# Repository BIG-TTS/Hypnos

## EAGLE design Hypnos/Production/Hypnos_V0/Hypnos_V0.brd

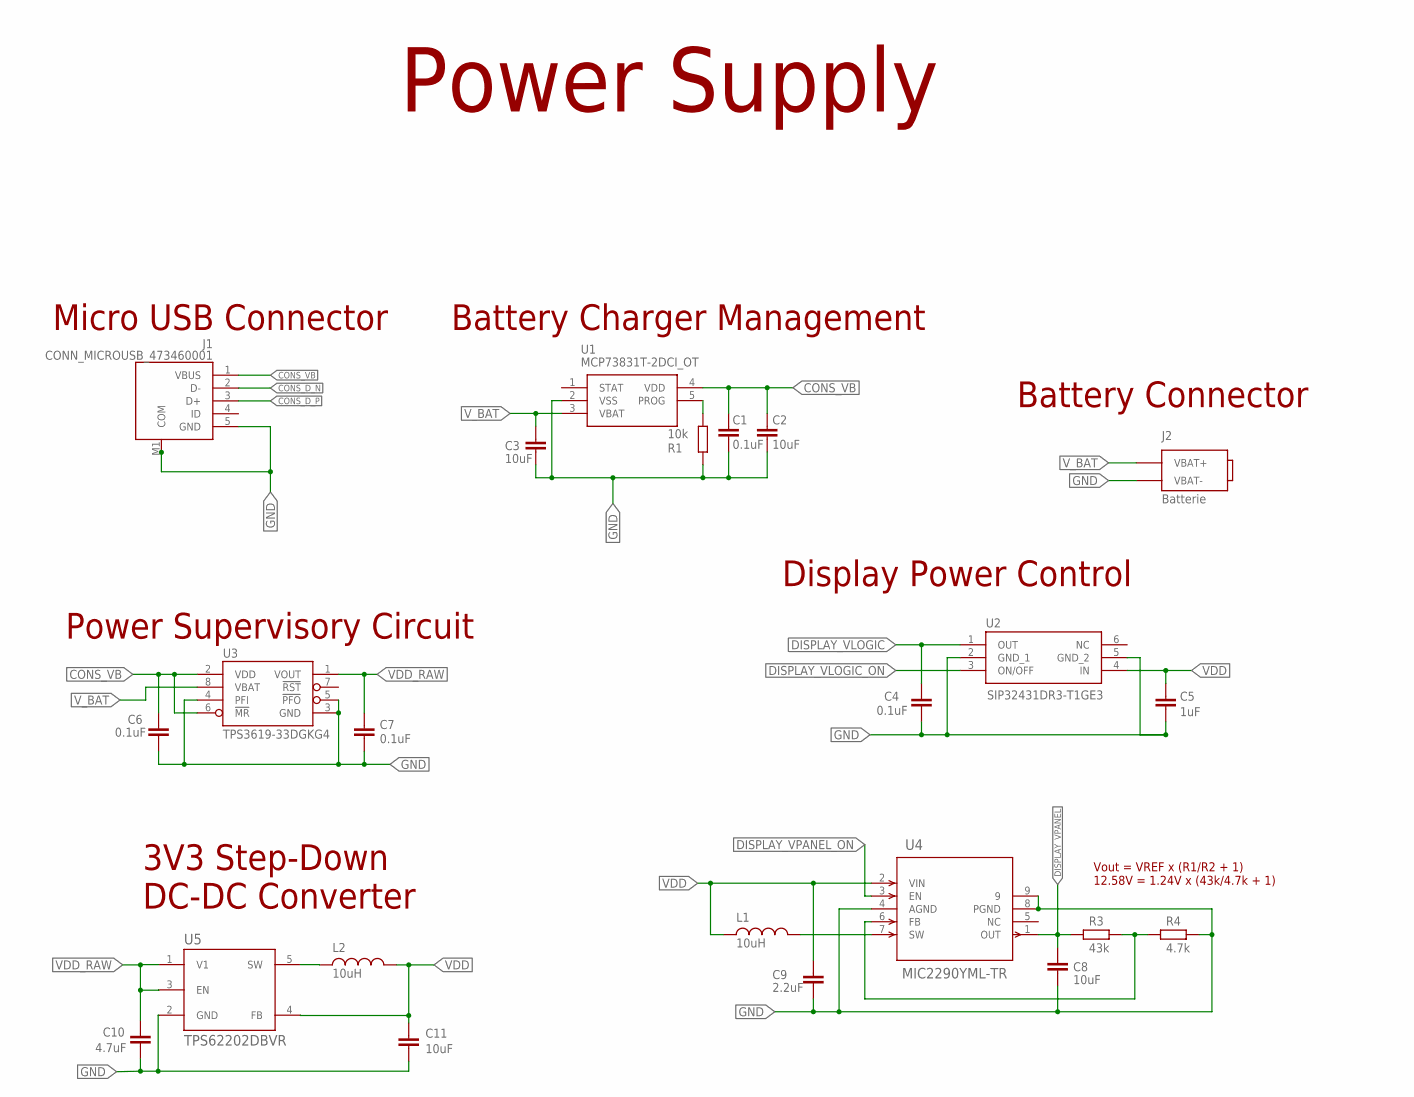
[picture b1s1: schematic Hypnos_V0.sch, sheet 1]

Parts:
C1, C4, C6, C7: 0.1uF; C0603K
C2, C3, C8, C11: 10uF; C0603K
C5: 1uF; C0603K
C9: 2.2uF; C0603K
C10: 4.7uF; C0603K
J1: CONN_MICROUSB_473460001; CONN_MOLEX_473460001
J2: Batterie; BATTERIE
L1, L2: 10uH; L1210
R1: 10k; R0603
R3: 43k; R0603
R4: 4.7k; R0603
U1: MCP73831T-2DCI_OT; SOT95P270X145-5N
U2: SIP32431DR3-T1GE3; SOT65P210X110-6N
U3: TPS3619-33DGKG4; MSOP8
U4: MIC2290YML-TR; MLF-8_ML_MCH
U5: TPS62202DBVR; SOT95P280X145-5N

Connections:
CONS_D_N: J1.2 (D-); also elsewhere on the board
CONS_D_P: J1.3 (D+); also elsewhere on the board
CONS_VB: C1.1, C2.1, C6.1, J1.1 (VBUS), U1.4 (VDD), U3.2 (VDD), U3.6 (!MR); also elsewhere on the board
DISPLAY_VLOGIC: C4.1, U2.1 (OUT); also elsewhere on the board
DISPLAY_VLOGIC_ON: U2.3 (ON/OFF); also elsewhere on the board
DISPLAY_VPANEL: C8.1, R3.2, U4.1 (OUT); also elsewhere on the board
DISPLAY_VPANEL_ON: U4.3 (EN); also elsewhere on the board
FB: R3.1, R4.2, U4.6 (FB)
GND: C1.2, C2.2, C3.2, C4.2, C5.2, C6.2, C7.2, C8.2, C9.2, C10.2, C11.2, J1.5 (GND), J1.M1 (COM), J1.M2 (COM), J1.M3 (COM), J1.M4 (COM), J1.M5 (COM), J1.M6 (COM), J2.2 (VBAT-), R1.2, R4.1, U1.2 (VSS), U2.2 (GND_1), U2.5 (GND_2), U3.3 (GND), U3.4 (PFI), U3.5 (!PFO), U4.4 (AGND), U4.8 (PGND), U4.9, U5.2 (GND); also elsewhere on the board
unnamed: L2.1, U5.5 (SW)
PROG: R1.1, U1.5 (PROG)
SW: L1.2, U4.7 (SW)
VDD: C5.1, C9.1, C11.1, L1.1, L2.2, U2.4 (IN), U4.2 (VIN), U5.4 (FB); also elsewhere on the board
VDD_RAW: C7.1, C10.1, U3.1 (VOUT), U5.1 (V1), U5.3 (EN)
V_BAT: C3.1, J2.1 (VBAT+), U1.3 (VBAT), U3.8 (VBAT)

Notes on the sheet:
Micro USB Connector
Battery Charger Management
Power Supervisory Circuit
Power Supply
3V3 Step-Down DC-DC Converter
Battery Connector
Display Power Control
Vout = VREF x (R1/R2 + 1) 12.58V = 1.24V x (43k/4.7k + 1)

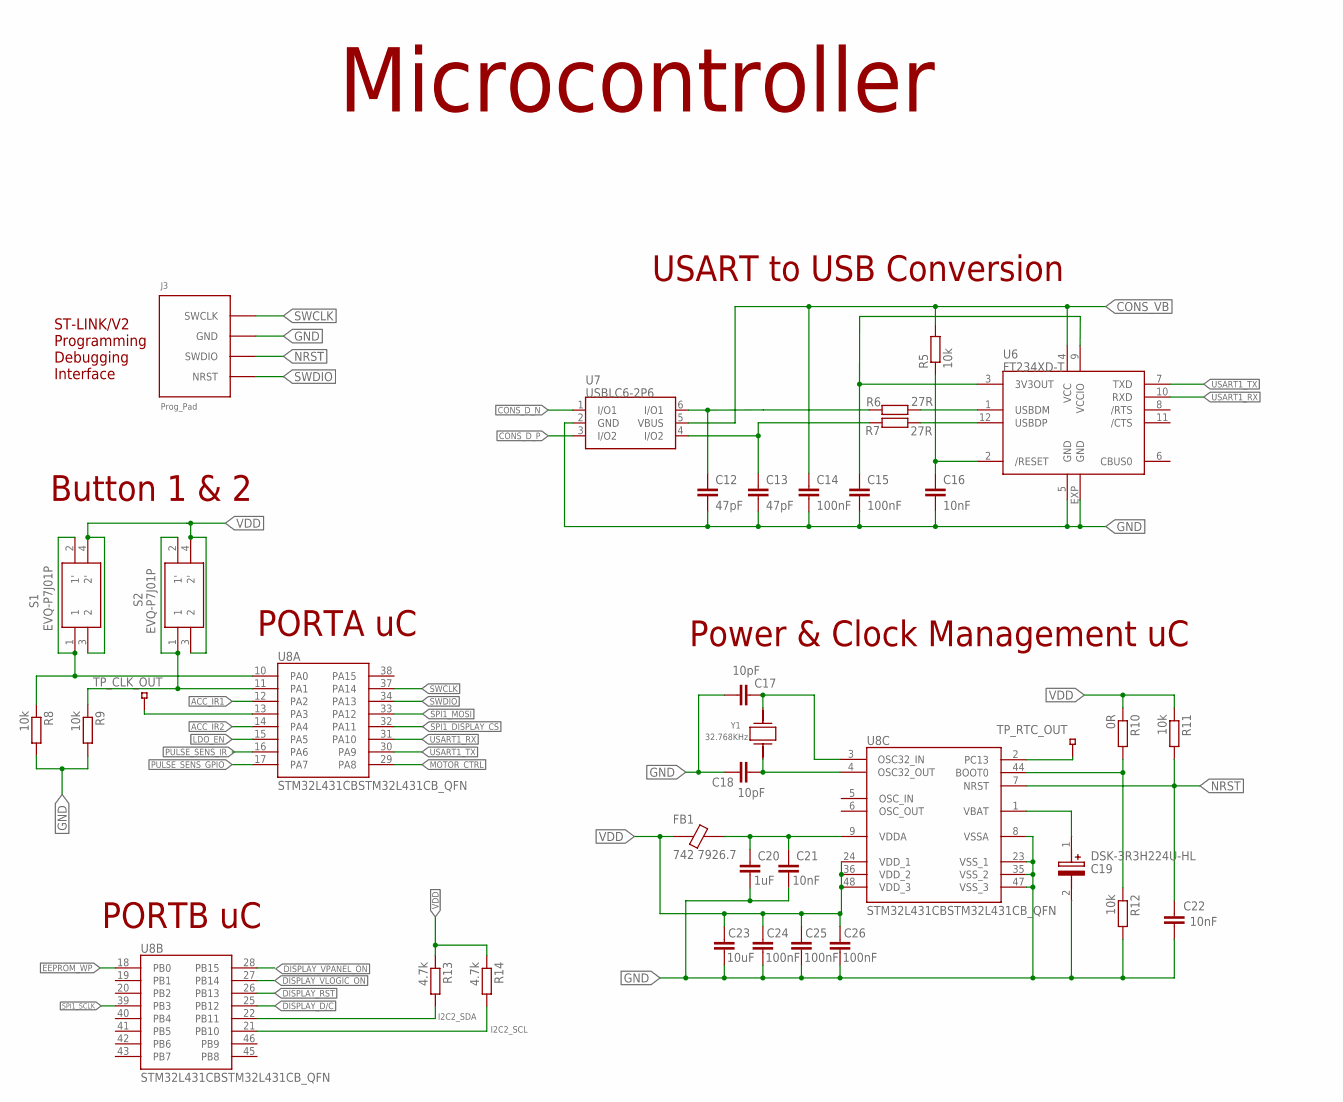
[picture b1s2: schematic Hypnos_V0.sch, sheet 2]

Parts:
C12, C13: 47pF; C0603K
C14, C15, C24, C25, C26: 100nF; C0603K
C16, C21, C22: 10nF; C0603K
C17, C18: 10pF; C0603K
C19: DSK-3R3H224U-HL; DSK3R3H334THL
C20: 1uF; C0603K
C23: 10uF; C0603K
FB1: 742 7926.7; FB0603
J3: Prog_Pad; PROG_PAD
R5, R8, R9, R11, R12: 10k; R0603
R6, R7: 27R; R0603
R10: 0R; R0603
R13, R14: 4.7k; R0603
S1, S2: EVQ-P7J01P; EVQP7J01P
TP_CLK_OUT: TEST_PIN_SMD; SMD_1
TP_RTC_OUT: TEST_PIN_SMD; SMD_1
U6: FT234XD-T; DFN12-3X3
U7: USBLC6-2P6; SOT666
U8: STM32L431CBSTM32L431CB_QFN; QFN50P700X700X60-49N
Y1: 32.768KHz; CM315

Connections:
/RESET: C16.1, R5.1, U6.2 (/RESET)
ACC_IR1: U8.12 (PA2); also elsewhere on the board
ACC_IR2: U8.14 (PA4); also elsewhere on the board
BUTTON1: R8.1, S1.1, S1.2 (1'), U8.10 (PA0)
BUTTON2: R9.1, S2.1, S2.2 (1'), U8.11 (PA1)
CLK_OUT: TP_CLK_OUT.P$1, U8.13 (PA3)
CONS_D_N: U7.1 (I/O1); also elsewhere on the board
CONS_D_P: U7.3 (I/O2); also elsewhere on the board
CONS_VB: C14.1, R5.2, U6.4 (VCC), U7.5 (VBUS); also elsewhere on the board
DISPLAY_D/C: U8.25 (PB12); also elsewhere on the board
DISPLAY_RST: U8.26 (PB13); also elsewhere on the board
DISPLAY_VLOGIC_ON: U8.27 (PB14); also elsewhere on the board
DISPLAY_VPANEL_ON: U8.28 (PB15); also elsewhere on the board
EEPROM_WP: U8.18 (PB0); also elsewhere on the board
GND: C12.2, C13.2, C14.2, C15.2, C16.2, C17.2, C18.2, C19.2 (-), C20.2, C21.2, C22.2, C23.2, C24.2, C25.2, C26.2, J3.2 (GND), R8.2, R9.2, R12.2, U6.5 (GND), U6.EXP (GND), U7.2 (GND), U8.8 (VSSA), U8.23 (VSS_1), U8.35 (VSS_2), U8.47 (VSS_3); also elsewhere on the board
I2C2_SCL: R14.2, U8.21 (PB10); also elsewhere on the board
I2C2_SDA: R13.2, U8.22 (PB11); also elsewhere on the board
LDO_EN: U8.15 (PA5); also elsewhere on the board
MOTOR_CTRL: U8.29 (PA8); also elsewhere on the board
unnamed: C18.1, U8.4 (OSC32_OUT), Y1.P$2
unnamed: C17.1, U8.3 (OSC32_IN), Y1.P$1
unnamed: C19.1 (+), U8.1 (VBAT)
unnamed: R10.2, R12.1, U8.44 (BOOT0)
unnamed: C13.1, R7.2, U7.4 (I/O2)
unnamed: C12.1, R6.2, U7.6 (I/O1)
NRST: C22.1, J3.3 (SWDIO), R11.2, U8.7 (NRST)
PULSE_SENS_GPIO: U8.17 (PA7); also elsewhere on the board
PULSE_SENS_IR: U8.16 (PA6); also elsewhere on the board
RTC_OUT: TP_RTC_OUT.P$1, U8.2 (PC13)
SPI1_DISPLAY_CS: U8.32 (PA11); also elsewhere on the board
SPI1_MOSI: U8.33 (PA12); also elsewhere on the board
SPI1_SCLK: U8.39 (PB3); also elsewhere on the board
SWCLK: J3.1 (SWCLK), U8.37 (PA14)
SWDIO: J3.4 (NRST), U8.34 (PA13)
USART1_RX: U6.10 (RXD), U8.31 (PA10)
USART1_TX: U6.7 (TXD), U8.30 (PA9)
USBDM: R6.1, U6.1 (USBDM)
USBDP: R7.1, U6.12 (USBDP)
VCCIO: C15.1, U6.3 (3V3OUT), U6.9 (VCCIO)
VDD: C23.1, C24.1, C25.1, C26.1, FB1.1, R10.1, R11.1, R13.1, R14.1, S1.3 (2), S1.4 (2'), S2.3 (2), S2.4 (2'), U8.24 (VDD_1), U8.36 (VDD_2), U8.48 (VDD_3); also elsewhere on the board
VDDA: C20.1, C21.1, FB1.2, U8.9 (VDDA)

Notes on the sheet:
ST-LINK/V2 Programming Debugging Interface
USART to USB Conversion
Power & Clock Management uC
PORTA uC
PORTB uC
Microcontroller
Button 1 & 2

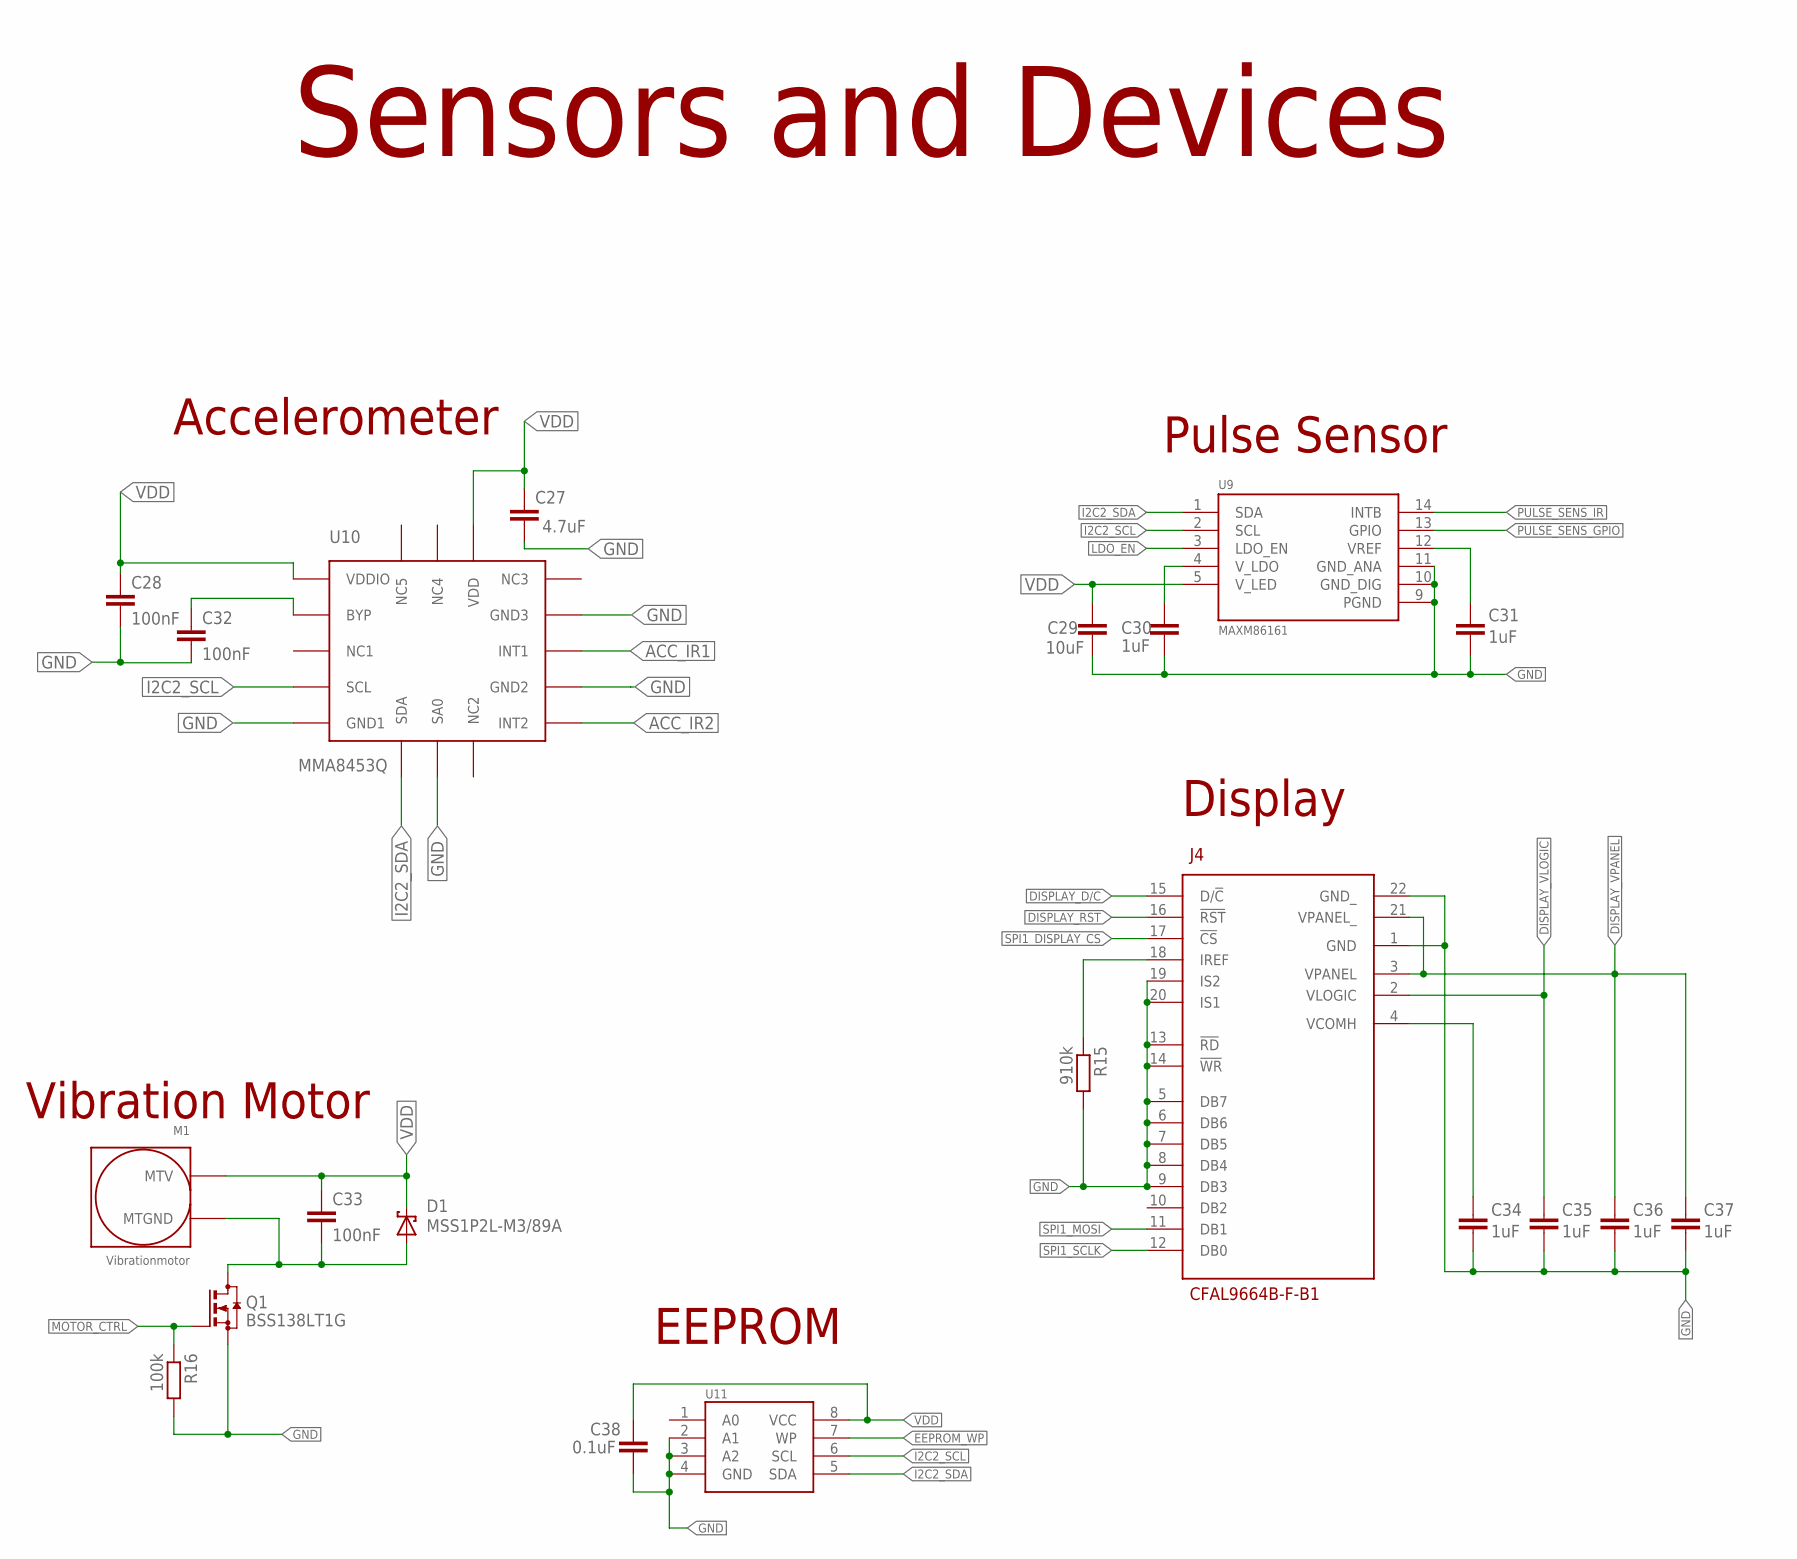
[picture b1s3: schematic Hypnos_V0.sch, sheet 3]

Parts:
C27: 4.7uF; C0603K
C28, C32, C33: 100nF; C0603K
C29: 10uF; C0603K
C30, C31, C34, C35, C36, C37: 1uF; C0603K
C38: 0.1uF; C0603K
D1: MSS1P2L-M3/89A; MICROSMP
J4: CFAL9664B-F-B1
M1: Vibrationmotor; VIBRATIONMOTOR
Q1: BSS138LT1G; SOT23
R15: 910k; R0603
R16: 100k; R0603
U9: MAXM86161
U10: MMA8453Q; QFN-COL
U11: BR24T1MFJ-3AME2; SOIC127P600X165-8N

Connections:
ACC_IR1: U10.P$11 (INT1); also elsewhere on the board
ACC_IR2: U10.P$9 (INT2); also elsewhere on the board
BYP: C32.1, U10.P$2 (BYP)
DISPLAY_D/C: J4.15 (D/!C); also elsewhere on the board
DISPLAY_RST: J4.16 (!RST); also elsewhere on the board
DISPLAY_VLOGIC: C35.1, J4.2 (VLOGIC); also elsewhere on the board
DISPLAY_VPANEL: C36.1, C37.1, J4.3 (VPANEL), J4.21 (VPANEL_); also elsewhere on the board
EEPROM_WP: U11.7 (WP); also elsewhere on the board
GND: C27.2, C28.2, C29.2, C30.2, C31.2, C32.2, C34.2, C35.2, C36.2, C37.2, C38.2, J4.1 (GND), J4.5 (DB7), J4.6 (DB6), J4.7 (DB5), J4.8 (DB4), J4.9 (DB3), J4.13 (!RD!), J4.14 (!WR!), J4.19 (IS2), J4.20 (IS1), J4.22 (GND_), Q1.2 (S), R15.2, R16.2, U9.9 (PGND), U9.10 (GND_DIG), U9.11 (GND_ANA), U10.P$5 (GND1), U10.P$7 (SA0), U10.P$10 (GND2), U10.P$12 (GND3), U11.2 (A1), U11.3 (A2), U11.4 (GND); also elsewhere on the board
I2C2_SCL: U9.2 (SCL), U10.P$4 (SCL), U11.6 (SCL); also elsewhere on the board
I2C2_SDA: U9.1 (SDA), U10.P$6 (SDA), U11.5 (SDA); also elsewhere on the board
IREF: J4.18 (IREF), R15.1
LDO_EN: U9.3 (LDO_EN); also elsewhere on the board
MOTOR_CTRL: Q1.1 (G), R16.1; also elsewhere on the board
MTGND: C33.2, D1.A, M1.1 (MTGND), Q1.3 (D)
PULSE_SENS_GPIO: U9.13 (GPIO); also elsewhere on the board
PULSE_SENS_IR: U9.14 (INTB); also elsewhere on the board
SPI1_DISPLAY_CS: J4.17 (!CS); also elsewhere on the board
SPI1_MOSI: J4.11 (DB1); also elsewhere on the board
SPI1_SCLK: J4.12 (DB0); also elsewhere on the board
VCOMH: C34.1, J4.4 (VCOMH)
VDD: C27.1, C28.1, C29.1, C33.1, C38.1, D1.C, M1.2 (MTV), U9.5 (V_LED), U10.P$1 (VDDIO), U10.P$14 (VDD), U11.8 (VCC); also elsewhere on the board
V_LDO: C30.1, U9.4 (V_LDO)
V_REF: C31.1, U9.12 (VREF)

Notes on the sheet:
Accelerometer
EEPROM
Pulse Sensor
Sensors and Devices
Vibration Motor
Display

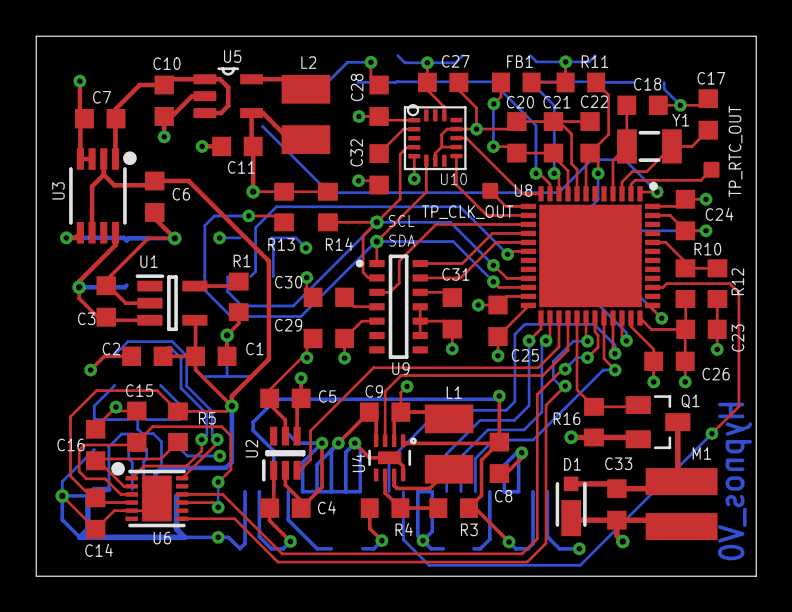
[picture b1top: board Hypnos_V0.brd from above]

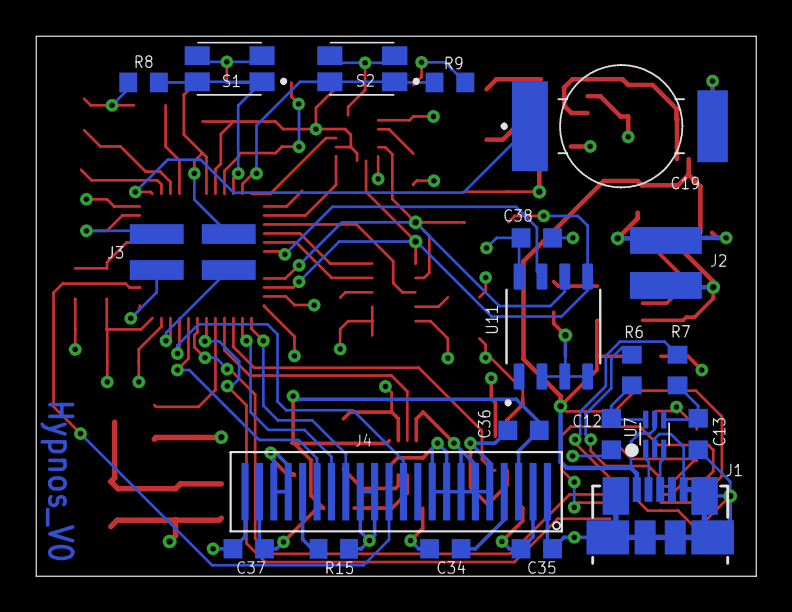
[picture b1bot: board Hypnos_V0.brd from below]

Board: 4 copper layers, 40.0 x 30.0 mm, 80 parts (21 on the bottom side), 55 nets.

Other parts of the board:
DRILEGEND: DRILEGEND

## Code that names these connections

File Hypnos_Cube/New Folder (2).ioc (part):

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Mcu.Name=STM32L431C(B-C)Tx
Mcu.Package=LQFP48
Mcu.UserName=STM32L431CBTx
PA0.Signal=S_TIM2_CH1
PA1.Signal=S_TIM2_CH2
PA10.Mode=Asynchronous
PA10.Signal=USART1_RX
PA11.Signal=GPIO_Output
PA12.Mode=Simplex_Bidirectional_Master
PA12.Signal=SPI1_MOSI
PA13\ (JTMS-SWDIO).Signal=SYS_JTMS-SWDIO
PA14\ (JTCK-SWCLK).Signal=SYS_JTCK-SWCLK
PA2.Signal=GPXTI2
PA3.Signal=S_TIM15_CH2
PA4.Signal=GPXTI4
PA5.Signal=GPXTI5
PA6.Signal=GPIO_Output
PA7.Signal=GPIO_Output
PA8.Signal=GPIO_Output
PA9.Mode=Asynchronous
PA9.Signal=USART1_TX
PB0.Signal=GPIO_Output
PB1.Signal=GPIO_Output
PB10.Mode=I2C
PB10.Signal=I2C2_SCL
PB11.Mode=I2C
PB11.Signal=I2C2_SDA
PB12.Signal=GPIO_Output
PB13.Signal=GPIO_Output
PB14.Signal=GPIO_Output
PB15.Signal=GPIO_Output
PB3\ (JTDO-TRACESWO).Mode=Simplex_Bidirectional_Master
PB3\ (JTDO-TRACESWO).Signal=SPI1_SCK
PC14-OSC32_IN\ (PC14).Mode=LSE-External-Oscillator
PC14-OSC32_IN\ (PC14).Signal=RCC_OSC32_IN
PC15-OSC32_OUT\ (PC15).Mode=LSE-External-Oscillator
PC15-OSC32_OUT\ (PC15).Signal=RCC_OSC32_OUT
RCC.HSE_VALUE=8000000
RCC.SYSCLKFreq_VALUE=80000000
RCC.SYSCLKSource=RCC_SYSCLKSOURCE_PLLCLK
board=custom

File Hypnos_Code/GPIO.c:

#include "common.h"

void GPIO_init(void)
{
	//Enable GPIO clock
	RCC ->AHB2ENR |= RCC_AHB2ENR_GPIOAEN;	//Enable Peripheral Clock for GPIOA
	RCC ->AHB2ENR |= RCC_AHB2ENR_GPIOBEN;	//Enable Peripheral Clock for GPIOB
	
	//Configure all GPIOS in analog mode to lower current consumption
	//GPIOA ->MODER |= 0xFFFFFFFF;
	//GPIOB ->MODER |= 0xFFFFFFFF;
	
	//Initialization of GPIO Pins for USART1	
	GPIOA ->MODER &= ~(GPIO_MODER_MODE9 | GPIO_MODER_MODE10);	//Reset PA9 and PA10 modes
	GPIOA ->MODER |= (GPIO_MODER_MODE9_1 | GPIO_MODER_MODE10_1);	//Configure PA9 and PA10 as alternate function
	GPIOA ->OTYPER &= ~(GPIO_OTYPER_OT9 | GPIO_OTYPER_OT10);	//Configure PA9 and PA10 as push pull
	GPIOA ->OSPEEDR |= (GPIO_OSPEEDR_OSPEED9 | GPIO_OSPEEDR_OSPEED10);	//Configure speed to the maximum
	GPIOA ->PUPDR &= ~(GPIO_PUPDR_PUPD9 | GPIO_PUPDR_PUPD10);	//No pull up or pull down
  GPIOA ->AFR[1] &= ~(GPIO_AFRH_AFSEL9 | GPIO_AFRH_AFSEL10);	//Reset alternate function mapping
	GPIOA ->AFR[1] |= (0x7 <<GPIO_AFRH_AFSEL9_Pos);	//Map PA9 to alternate function 7
	GPIOA ->AFR[1] |= (0x7 <<GPIO_AFRH_AFSEL10_Pos);	//Map PA10 to alternate function 7
	
	//Initialization of GPIO Pins for I2C 
	GPIOB ->MODER &= ~(GPIO_MODER_MODE11 | GPIO_MODER_MODE10);	//Reset PB11 and PB10 modes
	GPIOB ->MODER |= (GPIO_MODER_MODE11_1 | GPIO_MODER_MODE10_1);	//Configure PB11 and PB10 as alternate function
	GPIOB ->OTYPER |= (GPIO_OTYPER_OT11 | GPIO_OTYPER_OT10);	//Configure PB11 and PB10 as open drain
	GPIOB ->OSPEEDR |= (GPIO_OSPEEDR_OSPEED11 | GPIO_OSPEEDR_OSPEED10);	//Configure speed to the maximum
	GPIOB ->PUPDR &= ~(GPIO_PUPDR_PUPD11 | GPIO_PUPDR_PUPD10);	//No pull up or pull down
  GPIOB ->AFR[1] &= ~(GPIO_AFRH_AFSEL10 | GPIO_AFRH_AFSEL11);	//Reset alternate function mapping
	GPIOB ->AFR[1] |= (0x4 <<GPIO_AFRH_AFSEL10_Pos);	//Map PB10 to alternate function 4
	GPIOB ->AFR[1] |= (0x4 <<GPIO_AFRH_AFSEL11_Pos);	//Map PB11 to alternate function 4
	
	//Initialization of LDO_EN pin
	GPIOA ->MODER &= ~(GPIO_MODER_MODE5);	//Reset PA5 Mode
	GPIOA ->MODER |= GPIO_MODER_MODE5_0;	//Configure PA5 as output
	GPIOA ->OTYPER &= ~(GPIO_OTYPER_OT5);	//Configure PA5 output as push-pull
	GPIOA ->OSPEEDR &= ~(GPIO_OSPEEDR_OSPEED5);	//Configure speed to minimum
	GPIOA ->PUPDR &= ~(GPIO_PUPDR_PUPD5);	//No pull up or pull down
	
	//Initialization of MOTOR_CTRL pin
	GPIOA ->MODER &= ~(GPIO_MODER_MODE8);	//Reset PA8 Mode
	GPIOA ->MODER |= GPIO_MODER_MODE8_0;	//Configure PA8 as output
	GPIOA ->OTYPER &= ~(GPIO_OTYPER_OT8);	//Configure PA8 output as push-pull
	GPIOA ->OSPEEDR &= ~(GPIO_OSPEEDR_OSPEED8);	//Configure speed to minimum
	GPIOA ->PUPDR &= ~(GPIO_PUPDR_PUPD8);	//No pull up or pull down
	
	//Initialization of EEPROM_WP pin
	GPIOB ->MODER &= ~(GPIO_MODER_MODE0);	//Reset PB0 Mode
	GPIOB ->MODER |= GPIO_MODER_MODE0_0;	//Configure PB0 as output
	GPIOB ->OTYPER &= ~(GPIO_OTYPER_OT0);	//Configure PB0 output as push-pull
	GPIOB ->OSPEEDR &= ~(GPIO_OSPEEDR_OSPEED0);	//Configure speed to minimum
	GPIOB ->PUPDR &= ~(GPIO_PUPDR_PUPD0);	//No pull up or pull down
	
	//Initialization of display control pins (VPANEL_ON, VLOGIC_ON, RST, D/C)
	GPIOB ->MODER &= ~(GPIO_MODER_MODE12 | GPIO_MODER_MODE13 | GPIO_MODER_MODE14 | GPIO_MODER_MODE15);	//Reset PB12-PB15 Mode
	GPIOB ->MODER |= (GPIO_MODER_MODE12 | GPIO_MODER_MODE13 | GPIO_MODER_MODE14 | GPIO_MODER_MODE15);	//Configure PB12-PB15 as output
	GPIOB ->OTYPER &= ~(GPIO_OTYPER_OT12 | GPIO_OTYPER_OT13 | GPIO_OTYPER_OT14 | GPIO_OTYPER_OT15);	//Configure PB12-PB15 output as push-pull
	GPIOB ->OSPEEDR &= ~(GPIO_OSPEEDR_OSPEED12 | GPIO_OSPEEDR_OSPEED13 | GPIO_OSPEEDR_OSPEED14 | GPIO_OSPEEDR_OSPEED15);	//Configure speed to minimum
	GPIOB ->PUPDR &= ~(GPIO_PUPDR_PUPD12 | GPIO_PUPDR_PUPD13 | GPIO_PUPDR_PUPD14 | GPIO_PUPDR_PUPD15);	//No pull up or pull down	
	
	//tst
	GPIOA ->MODER &= ~(GPIO_MODER_MODE3);	//Reset PA5 Mode
	GPIOA ->MODER |= GPIO_MODER_MODE3_0;	//Configure PA5 as output
	GPIOA ->OTYPER &= ~(GPIO_OTYPER_OT3);	//Configure PA5 output as push-pull
	GPIOA ->OSPEEDR &= ~(GPIO_OSPEEDR_OSPEED3);	//Configure speed to minimum
	GPIOA ->PUPDR &= ~(GPIO_PUPDR_PUPD3);	//No pull up or pull down
}

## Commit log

2021-01-14 Added files from Hypnos: state not much further than BMA hand in
2021-06-02 Add files via upload
    BIO Sensor schickt Daten über Serielle SChnittstelle USART, Daten werden allerdings noch nicht verarbeitet.

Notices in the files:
parts and their libraries:
MIC2290YML-TR: COPYRIGHT: Copyright (C) 2018 Accelerated Designs. All rights reserved
